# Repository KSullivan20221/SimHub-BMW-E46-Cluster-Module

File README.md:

# SimHub-BMW-E46-Cluster-Module
This repo contains all of the circuitry, code, and resources used to create a shield board for an Arduino Mega that could be used to communicate with a BWM E46 instrument cluster from a PC. The main application of this project was in using the cluster in conjunction with SimHub in order to show the values from the supported video games on the cluster's gauges. 

All of the testing I performed was on an E46 cluster with the following ID number and firmware:  
* Cluster Serial Number: 1031098105  
* Cluster Hardware Number: 30  (Can retrieve this by running the on-board 'Test 1' on the cluster, in test 1.5)  
* Cluster Software Number: 360 (Can retrieve this by running the on-board 'Test 1' on the cluster, in test 1.5)  

See the following link for how to retreive this data: https://www.e46fanatics.com/threads/just-found-us-version-of-hidden-menu.239619/

## Credits

There is no way I could have accomplished this project without many of the resources available to me:
* I never would have got off the ground if it weren't for this pinout diagram for the cluster: https://www.bmwgm5.com/E46_IKE_Connections.htm
* I borrowed several functions / hardware connections from _Neuros-Projekte_, as well as most all of the KBUS communication methods: https://neuros-projekte.de/simulator/bmw-e46-arduino-simhub/
* Most all of the CAN communication was from the extensive research done by the users on this bimmerforums forum: https://www.bimmerforums.com/forum/showthread.php?1887229-E46-Can-bus-project
* amstudio on YouTube for introducing me to using SimHub, and providing a solid foundation to design my custom protocol on top of: https://www.youtube.com/watch?v=L59NL9EuEdM&ab_channel=amstudio

# Hardware Design
The circuit designed for this project was designed as a shield for an Arduino Mega microcontroller board. The purpose of this circuit was to take the signals from the Arduino Mega and use them to control the lights, gauges, and serial busses in the cluster. With this design, a user can supply 12V to the DC barrel jack input of the Arduino Mega in order to power the cluster, and then connect a USB-B cable from the computer running the video games to the Arduino to pass data between the computer and the Arduino. 

## Signals required to operate the cluster
In order to determine what signals I needed to drive the cluster, I searched for "E46 cluster pinout" and soon arrived at the following website which provided the pinout for the two connectors on the cluster:
https://www.bmwgm5.com/E46_IKE_Connections.htm

With this, and the help of the people on the following forum, I was able to come up with the following table outlining what signals were required at each pin of the cluster:

BMW CAN Bus Forum: https://www.bimmerforums.com/forum/showthread.php?1887229-E46-Can-bus-project

### X11175 Connector Pin Function / Signal Levels

| Pin Number | Pin Function                     	| Detailed Description                                                                     | Notes                                                                                                                                                            	|
| ---        | ---                              	| ---                                                                                      | ---   																			      																				|
| 1          | Ground                           	|                                                                                          |       																			      																				|
| 2          | Battery Charge Indicator         	| Provides a voltage up to 12 V indicating the batteries voltage level                     |       																			      																				|
| 3          | Engine Start Signal Feedback     	| Not certain, but seems like 12V into this pin indicates the engine has started           |       																			      																				|
| 4          | 12V Power input                  	| Always gets 12V from the battery                                                         |       																			      																				|
| 5          | 12V On / Start                   	| Receives 12V when car is fully on (key turned to second position)                        |       																			      																				|
| 6          | 12V Accessory / On / Start       	| Receives 12V when car is in accessory mode or when fully on                              |       																			      																				|
| 7          | Cluster backlight                	| On certain cluster models (not this one), setting to 12V turns backight on               |       																			      																				|
| 8          | Speedometer Signal Output        	| Unknown what this does, the cluster I used did not have anything wired here              |       																			      																				|
| 9          | CAN-H Signal                     	| The CAN High side of the differential pair                                               |       																			      																				|
| 10         | CAN-L Signal                     	| The CAN Low side of the differential pair                                                |       																			      																				|
| 11         | Fuel Tank 1 +                    	| Pin that fuel tank 1 level sensor positive signal is connected to                        | 70 Ohms to ground = empty, 395 Ohms to ground = full 													      														|
| 12         | Fuel Tank 1 -                    	| Return connection for fuel tank 1 level sensor (sits at ground potential)                | Connecting this to ground does not cause issues for this circuit      											     											 	|
| 13         | Oil Pressure Switch              	| Connects to oil pressure sensor                                                          | Pulling down to ground = oil pressure issue, leaving unconnected = no issue      										      										|
| 14         | K-Bus Signal                     	| K-Bus Communication signal                                                               | The K-Bus can be controlled by one of the Arduino's serial peripherals after being level-shifted so that it ranges from 0-12V instead of the Arduino's 0-5V      	|
| 15         | Fuel Tank 2 +                    	| Pin that fuel tank 2 level sensor positive signal is connected to                        | 70 Ohms to ground = empty, 310 Ohms to ground = full 													      														|
| 16         | Fuel Tank 2 -                    	| Return connection for fuel tank 2 level senor (sits at ground potential)                 | Connecting this to ground does not cause issues for this circuit      											      												|
| 17         | Oil Level Sensor                 	| Signal that measures how full the engine oil is                                          | Connecting this pin to ground indicates an issue with the oil level, leaving unconnected = no issue       							      							|
| 18         | Service Interval Indicator Reset 	| Not certain what purpose this serves                                                     |       																			      																				|
| 19         | Rear-Left Wheel Speed Sensor     	| Signal that connects to wheel speed sensor that drives the speedometer                   | This is driven by a 12V fixed 50% duty cycle variable frequency square-wave (about 31 Hz = 10 MPH, 1646 Hz = 155 MPH)      				      					|
| 20         | Brake Fluid Level Sensor         	| Signal that connects to brake fluid sensor                                               | Connecting this to ground indicates there is no issue with the brake fluid, leaving this unconnected indicates there is an issue      			      				|
| 21         | Airbag Warning LED               	| Indicates the passenger airbag is ready to engage                                        | Connecting this to ground indicates the airbag is ready to engage, and will illuminate the light on the dashboard  					      						|
| 22         | ABS Warning Light                	| Inicates that ABS is disabled                                                            | Connecting to ground indicates that ABS is active, and the thus the LED on the cluster will turn off, and vice versa 					      						|
| 23         | Parking brake switch             	| Indicates that the E-Brake is engaged                                                    | Connecting to ground indicates that the parking brake is not engaged, and will cause the 'BRAKE' light to turn off 					      						|
| 24         | Brake wear sensor                	| Indicates when the brakes are worn                                                       | Connecting to ground indicates that the brakes are not worn, and the cluster light will turn off, and vice versa 						      						|
| 25         | Diag Signal TX                   	| Unsure the function of this signal                                                       |       																			      																				|
| 26         | Coolant Level Sensor             	| Indicates if the coolant level is too low                                                | Connecting this to ground indicates that the coolant level is sufficient, and will turn the cluster light off, and vice versa 				      					|

### X11176 Connector Pin Function / Signal Levels

| Pin Number | Pin Function                 			| Detailed Description                                      | Notes                                                                                                                             |
| ---        | ---                         		 		| ---                                                       | ---   																			      											|
| 1          | AT+ Outside Temperature					| Reads data from sensor on the outside temperature			| 3.07kOhm to ground = 95 degrees farenheit, 4.7kOhm to ground = 77 degrees farenheit, 7.33kOhm to ground = 59 degrees farenheit	|
| 2	     	 | AT- Outside Temperature					| Return connection for the outside temperature sensor		| Connecting this to ground does not cause issues for this circuit 												      				|
| 3 	     | Not connected							| N/A											   			|																				      												|
| 4 	     | Washer Fluid Level						| Indicates if the washer fluid level is too low			| Connecting to ground indicates that the washer fluid is filled, and clear the light on the instrument cluster, and vice versa		|
| 5 	     | Cruise Control Active	        		| Signal indicates if cruise control is acitve or not		| Connecting to ground indicates that cruise control is active												      					|
| 6	     	 | Signal Airbag Warning, rollover sensor   | Indicates rollover in convertible version of car			| Not sure the polarity of this light as it was not active on this version of the cluster									      	|
| 7	     	 | Reverse									| Only in manual transmission version of car				| Not sure the polarity of this light as it was not active on this version of the cluster									      	|
| 8 	     | Not connected							| N/A											   			|																				      												|
| 9 	     | Not connected							| N/A											   			|																				      												|
| 10 	     | Not connected							| N/A											   			|																				      												|
| 11 	     | Not connected							| N/A											   			|																				      												|
| 12	     | Drivers seat belt						| Light to indicate if the driver's seat belt is engaged	| Connecting to ground indicates that the driver's seat belt is engaged, and vice verse									      		|
| 13	     | BC Button on turn signal stalk			| 											   				| Connecting to ground indicates that the BC button is pressed												      					|
| 14 	     | Signal Gong								| ?											   				| Unsure, but felt like this might engage the beeper on certain models											      				|
| 15 	     | Not connected							| N/A											   			|																				      												|
| 16 	     | Not connected							| N/A											   			|																				      												|
| 17 	     | Not connected							| N/A											   			|																			      													|
| 18 	     | Not connected							| N/A											   			|																				      												|

## Sub-Circuits used in cluster module

### Basic Pull-Down Network

This circuit in essence acts like a switch: When the Arduino applies 5V to the input of the circuit, the MOSFET (the DMN67D8L-7 part) turn on, and pulls the cluster pin to ground. The current that flows in this case can be up to 30mA, so the part was selected so that it could handle at least this (the selected part can handle up to roughly 200 mA). If the Arduino applies 0V to the input of the circuit, the MOSFET turns off and the cluster pin is pulled back up to 12V. 

This circuit is used to control the following pins:  
X11175 Connector: 13, 17, 19, 20, 21, 22, 23, 24, 26  
X11176 Connector: 4, 5, 6, 7, 12, 13

## 5V to 12V Level Shifter

This circuit acts very similar to the basic pull-down network: If the Arduino applies 5V on the input of the circuit, Q6 will turn on (connect the cluster pin to 12V), and Q4 will turn off. If the Arduino applies 0V on the input of the circuit, Q6 will turn off, and Q4 will turn on (connect the cluster pin to ground). The 10 Ohm resistor was added to limit the current going into the pin the circuit is connected to. 

This circuit is used to control the following pins:
X11175 Connector: 2, 7
X11176 Connector: 14

## KBUS Level Shifter

When the Arduino applies 0V to this circuit, Q7 turns off, and pulls the gate of Q9 up to 5V. This turns on Q9, and thus applies 0V to cluster pin 14. When the Arduino applies 5V to this circuit, Q7 turns on, and pulls the gate of Q9 down to ground. This turns off Q9, and thus pulls cluster pin 14 up to 12V. This circuit is used to translate the 5V 'Serial' messages coming from the Arduino to 12V message signals that the cluster expects to see. 

## Ignition and Accessory Mode Circuits

When the Arduino applies 5V to this circuit, it turns on Q31, which then pulls the gate of Q32 down to ground. Q32 is a PMOS transistor, and thus this turns the FET 'ON' which then applies 12V to the cluster pin. When the Arduino applies 0V to this circuit, it turns Q31 off, which then pulls the gate of Q32 up to 12V. This turns the FET 'OFF' which then pulls the cluster pin down to ground.  

This circuit was used to control the ignition and accessory mode cluster pins (X11175 pins 5 and 6 respectively)

## SPI -> CAN Circuitry

This circuit is a direct copy of the circuit used on the MCP2515 SPI to CAN development boards, such as this one:

## Fuel Level Circuit

This circuit is known more commonly as a 'shunt-regulator' (similar to the popular TL431 part you can find available online). This circuit makes more sense when you consider what the circuit on the input of the cluster looks like for X11175 Pins 11 and 15 (Tank1+ and Tank2+ respectively):

In this more simplified circuit, I represent the digital potentiometer as a normal potentiometer, and show what the input of the cluster looks like for the Tank+ pins. The idea is that as we change the value of the potentiometer, the gain of the circuit changes and causes the voltage at the Tank+ pin to change accordingly.   

For example:  
If the potentiometer is set to 0 ohms, the tank+ pin will be set to roughly 0.65V. To the cluster, this would look just the same as connecting a 50 Ohm resistor from the pin to ground. In the case that the potentiometer is set to 5kOhms, the voltage at the take+ pin will be set to roughly 2.7 Volts, which looks just the same as if a 397 Ohms resistor was connected from the pin to ground.   

In this sense, the circuit acts as a variable resistor that we can set from the Arduino ranging between about 50 Ohms and 397 Ohms, which covers the normal operating range for this pin of a resistance value between 70 Ohms and 395 Ohms (see table above for tank+ pins). In theory, the same circuit could have also been used for the ambient temperature sensor, but I chose against this since it did not change system performance at all.

## Other Circuits

There are a few circuits in the design containing connectors, DIP switches, and other such items that I do not cover here as they are more self-explanatory, but if you would like to know about any other part of of the schematic design, please let me know.

# Arduino Code

For this project, I provided two main programs: E46_Cluster_Test, and main-simhub-code. The following section outlines these two programs, as well as the communication protocol that is common to both programs:

## E46_Cluster_Test

This program was created in order to perform basic tests on the cluster. After uploading this code, you can send commands from the serial monitor to the Arduino, and then the Arduino will interact with the cluster in order to carry out the desired function. You must send every command with the following syntax:

In addition, make sure the Arduino Serial monitor is setup as shown below (most importantly, have the baud rate set to 9600, and the line ending set to 'Newline'):

See the section _Valid Command / Argument Combos for both programs_ for a list of commands that you can send to the cluster, along with the effect each one has.

## main-simhub-code

This program was created in order to interface with the cluster through the computer software _SimHub_, which allows you to send data from racing games to an Arduino. This program receieves data from SimHub, and using the same methods as the _E46_Cluster_Test_ program, sets the cluster up to reflect the sent data. You have to upload this program to the Arduino before attempting to use the SimHub application, or else it will hijack the serial port and not let you program the Arduino until you close the application.   

In order to make this application work with the hardware, you need to do the following:

1. Upload the main-simhub-code sketch to your Arduino
2. Open SimHub, and Navigate to the following menu: Arduino -> My Hardware
3. Confirm that there is a device connected in this menu
4. Under the _Custom Protocol_ for this device, paste in the contents of the _JavaScript_Protocol.txt_ file, and be sure to check the _Use javascript_ box
5. Press OK at the bottom of the window

At this point, you should be able to launch games from the SimHub dashboard (ensure that you configure each game according to SimHub's instructions).

## Valid Command / Argument Combos for both programs

The following is a list of valid commands and arguments that you can send to the instrument cluster from both applications. You can send these commands directly through the serial monitor for the E46_Cluster_Test program, or through a Custom Protocol in SimHub:

| Command             | Valid Arguments                                           | Description                                                            				|
| ---                 | ---                                                       | ---                                                                    				|
| speed               | Integer between 1 and 163                                 | Sets the speedometer to the desired value in MPH                       				|
| rpm                 | Integer between 0 and 7000                                | Sets the tachometer to the desired value  in RPM                       				|
| temp                | Integer between 65 and 405                                | Sets the oil temperature gauge to the desired value in degrees celcius 				|
| ignition            | Either 1 or 0                                             | Turns the ignition state to on / off                                   				|
| accessory           | Either 1 or 0                                             | Turns the accessory state to on / off                                  				|
| fuel                | Integer between 1 and 100                                 | Sets the fuel gauge to the desired value (have to cycle 12V power to cluster to change immediately) |
| engineStateFeedback | Either 1 or 0                                             | No noticeable effect                                                   				|
| signalGong          | Either 1 or 0                                             | No noticeable effect                                                   				|
| bc_button           | Either 1 or 0                                             | No noticeable effect                                                   				|
| seatBelt            | Either 1 or 0                                             | No noticeable effect                                                          |
| coolantLevelSensor  | Either 1 or 0                                             | '0' causes the coolant light to come on, '1' turns it off (have to cycle ignition to change state)  |
| brakeWearSensor     | Either 1 or 0                                             | '0' causes the brake pad wear light to come on, '1' turns it off       				|
| parkingBrakeState   | Either 1 or 0                                             | '0' turns BRAKE light on, '1' turns it off                             				|
| ABS_Warning         | Either 1 or 0                                             | '0' turns ABS light on, '1' turns it off                               				|
| airbagLight         | Either 1 or 0                                             | '0' turns airbag light off, '1' turns it on                            				|
| brakeFluidSensor    | Either 1 or 0                                             | No noticeable effect                                                   				|
| oilSensor           | Either 1 or 0                                             | No noticeable effect                                                   				|
| oilPressureSwitch   | Either 1 or 0                                             | No noticeable effect                                                   				|
| clusterBacklight    | Either 1 or 0                                             | No noticeable effect                                                   				|
| washerFluidLight    | Either 1 or 0                                             | '1' turns the light off, '0' turns it on (have to cycle ignition to change                                                                        				|
| cruiseLight         | Either 1 or 0                                             |                                                                        				|
| rolloverSensor      | Either 1 or 0                                             |                                                                        				|
| reverse             | Either 1 or 0                                             |                                                                        				|
| eLight              | Either 1 or 0                                             | '1' turns the _Service Engine Soon_ light on, '0' turns off            				|
| emlLight            | Either 1 or 0                                             | '1' turns the _EML_ light on, '0' turns off                            				|
| gasCapLight         | Either 1 or 0                                             | '1' turns the _CHECK GAS CAP_ light on, '0' turns off                  				|
| heatLight           | Either 1 or 0                                             | '1' turns the over temperature light on, '0' turns off                 				|
| oilLight            | Either 1 or 0                                             | '1' turns the low oil pressure warning light on, '0' turns it off      				|
| chgLight            | Either 1 or 0                                             | '1' turns the battery charge light on, '0' turns it off                				|
| highBeam            | Either 1 or 0                                             | '1' turns the highbeam indicator on, '0' turns it off                  				|
| fogRear             | Either 1 or 0                                             | '1' turns the rear fog-light indicator on, '0' turns it off            				|
| fogFront            | Either 1 or 0                                             | '1' turns the front fog-light indicator on, '0' turns it off           				|
| leftBlink           | Either 1 or 0                                             | '1' turns the left blinker on, '0' turns it off                        				|
| rightBlink          | Either 1 or 0                                             | '1' turns the right blinker on, '0' turns it off                       				|
| backRightLight      | Either 1 or 0                                             | '1' turns the light on, '0' turns it off                               				|
| backLeftLight       | Either 1 or 0                                             | '1' turns the light on, '0' turns it off                               				|
| frontRightLight     | Either 1 or 0                                             | '1' turns the light on, '0' turns it off                               				|
| frontLeftLight      | Either 1 or 0                                             | '1' turns the light on, '0' turns it off                               				|
| carLight            | Either 1 or 0                                             | '1' turns the light on, '0' turns it off                               				|

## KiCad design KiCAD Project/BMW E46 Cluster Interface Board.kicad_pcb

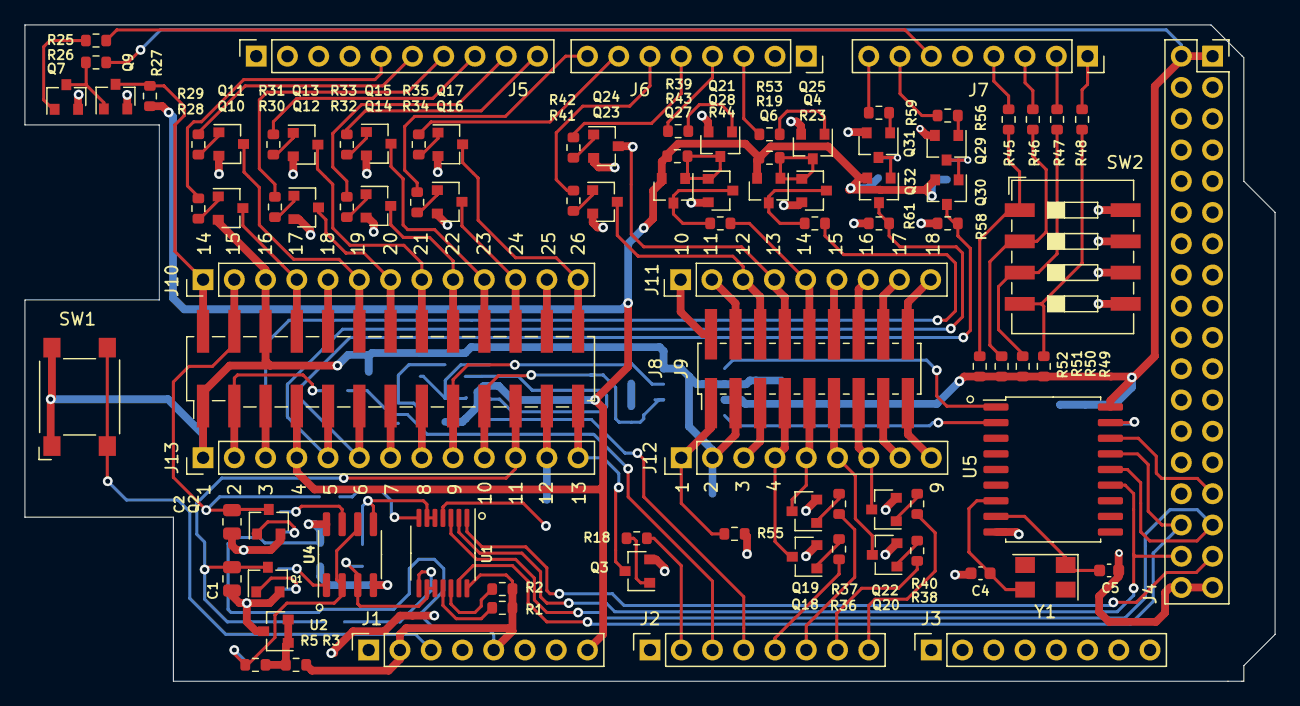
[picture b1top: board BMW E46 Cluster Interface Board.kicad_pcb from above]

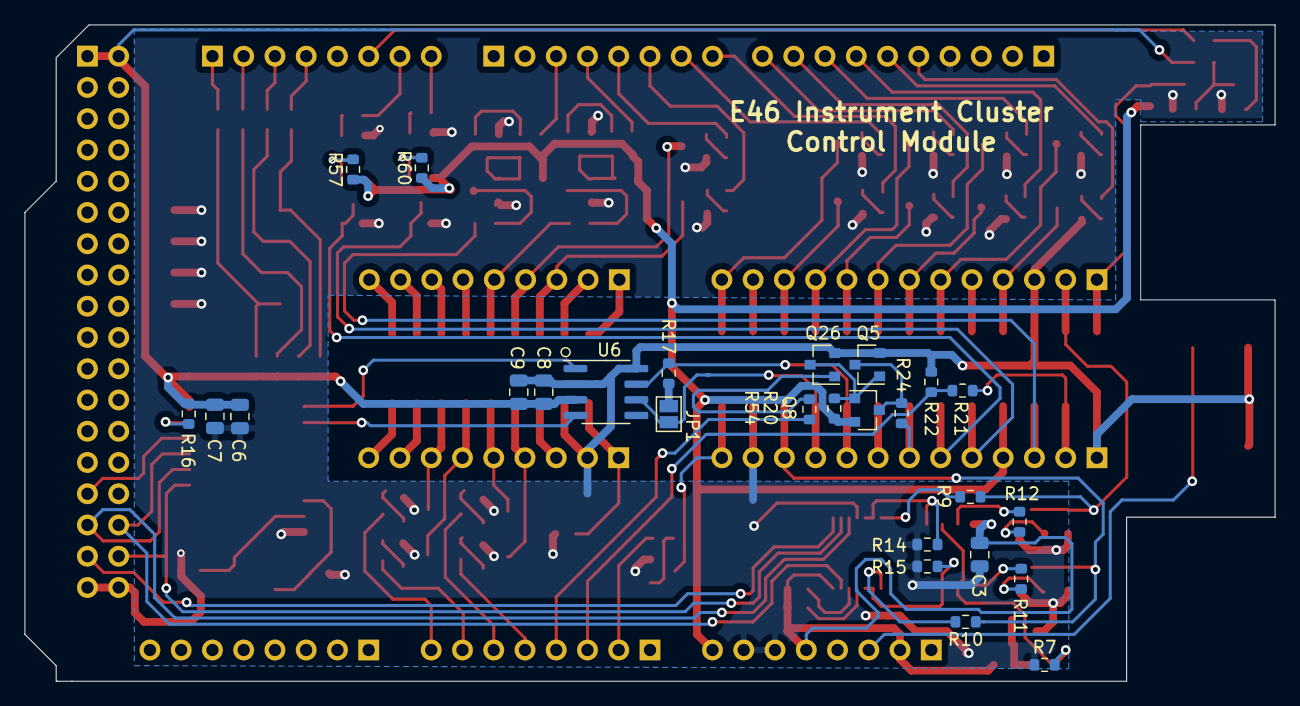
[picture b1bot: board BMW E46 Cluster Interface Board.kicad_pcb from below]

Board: 2 copper layers, 101.6 x 53.3 mm, 120 parts (26 on the bottom side), 126 nets.

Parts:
C1, C2: 1u; C_0805_2012Metric
C3, C6, C7, C8, C9: 0.1u; C_0805_2012Metric
C4, C5: 22p; C_0603_1608Metric
J1, J2, J3, J6, J7: Conn_01x08_Female; PinSocket_1x08_P2.54mm_Vertical
J4: Conn_02x18_Odd_Even; PinSocket_2x18_P2.54mm_Vertical
J5: Conn_01x10_Female; PinSocket_1x10_P2.54mm_Vertical
J8: Conn_02x13_Top_Bottom; 3020-26-0300-00
J9: Conn_02x09_Top_Bottom; PinHeader_2x09_P2.00mm_Vertical_SMD_Top_Bottom;98424-G52-18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
J10, J13: Conn_01x13; PinHeader_1x13_P2.54mm_Vertical
J11, J12: Conn_01x09; PinHeader_1x09_P2.54mm_Vertical
JP1: SolderJumper_2_Open; SolderJumper-2_P1.3mm_Open_Pad1.0x1.5mm
Q1, Q2, Q3, Q4, Q5, Q7, Q9, Q10, Q11, Q12, Q13, Q14, Q15, Q16, Q17, Q18, Q19, Q20, Q21, Q22, Q23, Q24, Q25, Q26, Q28, Q29, Q31: DMN67D8L-7; SOT-23
Q6, Q8, Q27, Q30, Q32: TP0610K-T1-E3; SOT-23
R1, R2, R7, R16, R19, R20, R26, R43, R45, R46, R47, R48, R49, R50, R51, R52, R55, R57, R58, R60, R61: 10k; R_0603_1608Metric
R3, R27: 1k; R_0603_1608Metric
R5: 90.9k; R_0603_1608Metric
R9, R10: 966; R_0603_1608Metric
R11, R12, R23, R24, R44: 10; R_0603_1608Metric
R14, R15: 604; R_0603_1608Metric
R17: 120; R_0603_1608Metric
R18, R25, R28, R29, R30, R31, R32, R33, R34, R35, R36, R37, R38, R39, R40, R41, R42, R53, R54, R56, R59: 100; R_0603_1608Metric
R21: 200k; R_0603_1608Metric
R22: 100k; R_0603_1608Metric
SW1: SW_MEC_5E; SW_SPST_Omron_B3FS-101xP
SW2: SW_DIP_x04; SW_DIP_SPSTx04_Slide_9.78x12.34mm_W8.61mm_P2.54mm
U1: MCP4251-xxxx-ST; TSSOP-14_4.4x5mm_P0.65mm
U2: TL431DBZ; SOT-23
U4: MCP6002T-I/SN; SOIC-8_3.9x4.9mm_P1.27mm
U5: MCP2515-xSO; SOIC-18W_7.5x11.6mm_P1.27mm
U6: TJA1050T-3; SOIC-8_3.9x4.9mm_P1.27mm
Y1: 8 MHz; Crystal_SMD_5032-4Pin_5.0x3.2mm

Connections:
0.25V_REF: R5.1, R7.2, U4.2, U4.6
12V-Accessory: J8.6, J13.6, Q30.3, R58.1
12V-On: J8.5, J13.5, Q32.3, R61.1
+5V: C3.2, C6.1, C7.1, C8.1, C9.1, J1.2, J1.5, J4.1, J4.2, R1.2, R2.2, R3.1, R16.1, R26.2, R49.1, R50.1, R51.1, R52.1, U1.14, U4.8, U5.18, U6.3
+12V: J1.8, J8.4, J13.4, Q6.2, Q8.2, Q27.2, Q30.2, Q32.2, R19.1, R20.1, R27.1, R43.1, R57.1, R60.1
A1: J2.2, R18.1
A2: J2.3, R21.1, R22.1
A3: J2.4, R54.2
A4: J2.5, R36.2
A5: J2.6, R37.2
A6: J2.7, R38.2
A7: J2.8, R40.2
ABS-Warning-Light: J8.22, J10.9, Q14.3
Airbag-Warning: J8.21, J10.8, Q13.3
BC-Button: J9.13, J11.4, Q24.3
Battery-Charge-Indicator: J8.2, J13.2, R21.2
Brake-Fluid-Sensor: J8.20, J10.7, Q12.3
Brake-Wear-Sensor: J8.24, J10.11, Q16.3
CAN_H: J8.9, J13.9, R17.1, U6.7
CAN_L: J8.10, J13.10, JP1.2, U6.6
Cluster-Backlight: J8.7, J13.7, R24.1
Coolant-Level-Sensor: J8.26, J10.13, Q17.3
Cruise-Control-Light: J9.5, J12.5, Q19.3
D2: J6.3, R53.2
D3: J6.4, R39.2
D4: J6.5, R42.2
D5: J6.6, R41.2
D6: J6.7, R35.2
D7: J6.8, R34.2
D8: J5.10, R33.2
D9: J5.9, R32.2
D10: J5.8, R31.2
D11: J5.7, R30.2
D12: J5.6, R29.2
D13: J5.5, R28.2
D14: J7.8, R59.2
D15: J7.7, R56.2
D16: J7.6, R25.1
D18: J7.4, R45.2
D19: J7.3, R46.2
D20: J7.2, R47.2
D21: J7.1, R48.2
DIGIPOT_CS: J4.33, U1.1
Engine-Start-Signal-Feedback: J8.3, J13.3, R23.1
FUEL-LEFT: C2.1, J8.15, J10.2, Q2.3, R9.1
FUEL-RIGHT: C1.1, J8.11, J13.11, Q1.3, R10.1
GND: C1.2, C2.2, C3.1, C4.2, C5.2, C6.2, C7.2, C8.2, C9.2, J1.6, J1.7, J4.35, J4.36, J5.4, J8.1, J8.12, J8.16, J9.2, J10.3, J12.2, J13.1, J13.12, Q1.2, Q2.2, Q3.2, Q4.2, Q5.2, Q7.2, Q9.2, Q10.2, Q11.2, Q12.2, Q13.2, Q14.2, Q15.2, Q16.2, Q17.2, Q18.2, Q19.2, Q20.2, Q21.2, Q22.2, Q23.2, Q24.2, Q25.2, Q26.2, Q28.2, Q29.2, Q31.2, R7.1, R14.2, R15.2, R22.2, R55.2, R58.2, R61.2, SW1.1, SW1.2, SW2.5, SW2.6, SW2.7, SW2.8, U1.4, U2.3, U4.4, U5.9, U6.2, U6.8
K_BUS: J8.14, J10.1, Q9.3, R27.2
MCP2515_CS: J4.29, U5.16
MISO: J4.32, U1.13, U5.15
MOSI: J4.31, U1.3, U5.14
NC1: J9.18, J11.9
NC2: J9.17, J11.8
NC3: J9.16, J11.7
NC4: J9.15, J11.6
NC5: J9.11, J11.2
NC6: J9.10, J11.1
NC7: J9.9, J12.9
NC8: J9.8, J12.8
NC9: J9.3, J12.3
unnamed: C4.1, U5.7, Y1.2
unnamed: C5.1, U5.8, Y1.1
unnamed: JP1.1, R17.2
unnamed: Q1.1, R11.1
unnamed: Q2.1, R12.1
unnamed: Q3.1, R18.2
unnamed: Q4.3, Q6.3, R23.2
unnamed: Q5.3, Q8.3, R24.2
unnamed: Q7.1, R25.2
unnamed: Q7.3, Q9.1, R26.1
unnamed: Q10.1, R28.1
unnamed: Q11.1, R29.1
unnamed: Q12.1, R30.1
unnamed: Q13.1, R31.1
unnamed: Q14.1, R32.1
unnamed: Q15.1, R33.1
unnamed: Q16.1, R34.1
unnamed: Q17.1, R35.1
unnamed: Q18.1, R36.1
unnamed: Q19.1, R37.1
unnamed: Q20.1, R38.1
unnamed: Q21.1, R39.1
unnamed: Q21.3, Q27.1, Q28.1, R43.2
unnamed: Q22.1, R40.1
unnamed: Q23.1, R41.1
unnamed: Q24.1, R42.1
unnamed: Q25.1, R53.1
unnamed: Q4.1, Q6.1, Q25.3, R19.2
unnamed: Q26.1, R54.1
unnamed: Q5.1, Q8.1, Q26.3, R20.2
unnamed: Q27.3, Q28.3, R44.2
unnamed: Q29.1, R56.1
unnamed: Q29.3, Q30.1, R57.2
unnamed: Q31.1, R59.1
unnamed: Q31.3, Q32.1, R60.2
unnamed: R1.1, U1.11
unnamed: R2.1, U1.12
unnamed: R3.2, R5.2, U2.1, U2.2
unnamed: R9.2, U1.7
unnamed: R10.2, U1.8
unnamed: R11.2, U4.1
unnamed: R12.2, U4.7
unnamed: R14.1, U1.5, U1.6, U4.5
unnamed: R15.1, U1.9, U1.10, U4.3
unnamed: R16.2, U5.17
unnamed: R45.1, R52.2, SW2.1
unnamed: R46.1, R51.2, SW2.2
unnamed: R47.1, R50.2, SW2.3
unnamed: R48.1, R49.2, SW2.4
unnamed: U5.1, U6.1
unnamed: U5.2, U6.4
OBDII-DIAG: J8.25, J10.12
Oil-Level-Sensor: J8.17, J10.4, Q10.3
Oil-Pressure-Switch: J8.13, J13.13, Q3.3
Outside-Temp: J9.1, J12.1, R55.1
Parking-Brake-Switch: J8.23, J10.10, Q15.3
RESET: J1.3, SW1.3, SW1.4
Reverse: J9.7, J12.7, Q22.3
Rollover-Sensor: J9.6, J12.6, Q20.3
SCK: J4.34, U1.2, U5.13
Seat-Belt: J9.12, J11.3, Q23.3
Service-Interval-Reset: J8.18, J10.5
Signal-Gong: J9.14, J11.5, R44.1
Speed-Signal: J8.19, J10.6, Q11.3
Speedometer-Signal-Output: J8.8, J13.8
Washer-Fluid-Level: J9.4, J12.4, Q18.3

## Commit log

2021-11-16 First upload of all codes / hardware files for this project
2021-11-16 Updated docstrings in Arduino code
2021-11-16 Updated javascript protocol for generic games section
2021-11-23 Updated the default configuration for the washer fluid circuit after testing
